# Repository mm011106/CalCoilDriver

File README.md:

<!-- 
基本資料はこちら：
BOXで、 ESM50902 を検索
SQUID用と比べて電流値が大きかも。
 -->

> [!NOTE]
> 資料などについてコメント等あればDiscussionsに投稿ください。

# 機器名
### **キャリブレーションコイルドライバ　ER-524D**

# 機器の概要

## 用途・目的
<!-- 本製品は磁気センサの感度・位置校正を行うための基準磁場を発生するためのコイルを定電流駆動する駆動回路です。
適切に設計・配置されたコイルでキャリブレーションコイルドライバにより基準となる磁場を発生させ、磁気センサから得られた磁場の強度信号とコイルドライバからの印加電流強度信号を以て磁気センサの感度・位置を校正することが可能です。 -->

複数の磁気センサをアレイ状に配置し磁場計測を行う場合、各センサ位置とその感度の両方を校正する必要があります。寸法や巻き数などのパラメタが管理されて製作されたコイル（キャリブレーションコイル）とそれを規定の電流で駆動する回路により基準となる磁場を発生させ、その磁場を計測することで校正が可能となります。この「キャリブレーションコイルドライバ」は校正作業に必要なキャリブレーションコイルを規定の電流で駆動するために設計された回路です。
> [!NOTE]
> 磁気センサの校正は以下の手順で行われます：
> 1. **センサとコイルの配置設定**：キャリブレーションコイル（複数）を校正対象の磁気センサに対して適切な位置に配置
> 2. **基準磁場の発生**：コイルドライバにより既知の強度の磁場を複数の異なる場所で発生させ、その磁場を校正対象のセンサで計測する
> 3. **信号計測**：発生した磁場の強度を磁気センサで測定すると同時に、コイルドライバのモニタ端子からコイルに流れた電流を計測
> 4. **校正実行**：両者の計測結果を基に磁気センサの感度と位置を校正

## 機能
- 交流の電流を各コイルに時分割で供給し駆動します。
- 各コイルの駆動はバースト波状の正弦波信号です。
- コイルを駆動する電流はパネルのスイッチで切り替えが可能です。
- コイルに流れる電流は電圧としてモニタができます。
- 流れている電流と上記のモニタ端子の電圧を測定器を用いて値づけすることにより、コイルに流れる電流値が計測できます。
- 単三型充電池4本で動作します。

## 性能
- 駆動信号周波数： 80Hz
- 駆動電流波形：正弦波
- 電流出力：200 / 100 / 20 / 10 [μAo-p]
- 駆動チャネル数：24（設計により変更可能）
 
> [!NOTE]
>  **駆動対象**
> 駆動の対象となるコイルは、十分直流インピーダンスが低く、インダクタンスが小さいことを想定しています。駆動回路の出力インピーダンスは10kΩ程度となっているため、コイルの直流インピーダンスが大きいと規定の電流を流せなくなる可能性があります（動作に支障はありません）。インダクタンスについては1mH以下を想定しています。駆動周波数80Hzでのコイルのインピーダンスが十分小さいことを条件として設計しています。
 <!-- 出力インピーダンス10kΩとして、1mH負荷のときのHPF遮断周波数は1.6MHz 一方、1mHの80Hzでのインピーダンス（リアクタンス）は0.5Ω -->

> [!NOTE]
>  **駆動回路**
> 駆動回路は高インピーダンス出力の非安定化電流源となっています。負荷接続時に定電流制御する回路は実装されていません。
> 負荷となるコイルがよく管理されて製造されているためコイルのインピーダンスのばらつきが非常に小さく、インピーダンスそのものも小さいと想定できたため、簡便な回路としました。

## バリエーション
本器の「負荷に電流を供給しその電流値を計測する」という機能により、生体磁場信号をエミュレートするための「ファントムコイル」をドライブすることに最適化した「ファントムドライバ」を作成可能です。磁場センサのキャリブレーションとは異なる電流設定（磁場強度設定）が必要な場合は出力電流の再設計が必要です。
> [!NOTE]
> **駆動電流の変更**
> 駆動電流の変更には回路定数の変更が必要となります。使用しているデバイスの性能から駆動電流の最大値は5mAo-p程度です。これ以上の電流が必要な場合は、回路定数の変更と同時にオペアンプの変更を検討してください。
>
> 

# 機器の構成 
コイルを駆動するための回路本体のみです。
キャリブレーションコイルそのものについては、この設計情報に含まれません。

# 動作の概要

### 駆動可能なコイルの数
この回路で駆動できるコイルの数は24個です。キャリブレーションコイルは３軸方向に磁場を発生させることを想定しており、３個のコイルが１つのコイルセットとなり、さらにそれを８個（３軸のコイルセットを８個）駆動できます。
駆動のための信号は多ピンコネクタ（ハーフピッチ50pin-SCSIコネクタ）に出力されますので、適宜コイルと接続するためのジグやケーブルの製作が必要となります。
> [!NOTE]
> 多ピンのコネクタは近年入手が困難になってきています。新たに製作される場合は3ピン〜6ピン程度の小型コネクタを複数利用するのが得策かと思います。

回路設計としては最大50個のコイルが駆動できるようになっていますので、ユーザの用途に応じてチャネル数を変更できます。

### 駆動波形
駆動は内部の正弦波発振回路に同期した正弦波のバースト波により時分割で行われます。駆動の様子を図示しました。
24個のコイルの駆動が1つのコイル駆動シーケンスとなり、それが繰り返されます。

まず、そのシーケンスの開始を示すため同期信号が正弦波の1周期の時間だけアサートされます。
同期信号がネゲートされると最初のコイルが駆動が始まります。
コイルは正弦波の24周期の時間だけ駆動され、1周期分の駆動休止時間が続き、次のコイルの駆動へと移ります。
最後のコイルが駆動された後、正弦波25周期分の長い駆動休止時間があり、コイルドライブの1周期が完了します。

駆動するコイルの順番やチャネル数、バースト波の波数と休止波数、正弦波の周波数は回路（HDL）で設定することができます。デフォルトでは、チャネル数24、正弦波の周波数80Hz、バースト波の波数24、休止波数1となっています。

<!-- 駆動用の正弦波は内部(DDSによる)で生成していますが、外部から供給することも可能です。この場合、信号の振幅が直接コイル駆動の電流値に変換されますので、供給する信号の振幅設定を確認してご利用ください。 -->

（下記「コイル駆動のタイミングチャート」を参照）

### 電流モニタ端子
コイルに流れる電流をモニタするための端子を備えています。
アナログ電圧出力で、0A = 1.65V となっています。
電流・電圧変換係数は、設計値で5033[V/I]となっています。

### 駆動電流の切り替え
駆動電流は、10μAo-p, 20μAo-p, 100μAo-p, 200μAo-pの４点切り替えです。
2つのトグルスイッチで設定します。

### 同期信号
24個のコイル駆動シーケンスの最初に正弦波の1周期の時間だけアサートされます。
レベルは0−3.3V、アクティブHi（正論理）です。

# 仕様
- ドライブコイル数：24
<br></br>
- 駆動電流 　(スイッチによる　4点切り替え)
  - 10/20/100/200μAo-p
<br></br>
- インターフェイス </br>
  - 同期信号出力：0−3.3Vロジック出力（正論理）
  - 駆動電流モニタ出力
    - アナログ電圧による（1.65V中心に+/-1V振幅）
    - 電流電圧変換係数：5033\[V/I] (設計値)
<br></br>
- 操作：フロントパネルトグルスイッチによる電源のOn/Off
<br></br>
- 表示
  - 電源電圧低下警告 Low-Battery（LED:赤）
  - 動作表示 (LED:緑)
<br></br>
- 電源：単三充電池（Ni-MH）4本
<br></br>

### コイル駆動のタイミングチャート
<!--  -->

### ブロック図

</br>

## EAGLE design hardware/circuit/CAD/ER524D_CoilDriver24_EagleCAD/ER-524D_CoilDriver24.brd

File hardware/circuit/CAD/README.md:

# このディレクトリについて
このディレクトリは回路図・基板CADのプロジェクトが保管されています。</br>

CADにはEAGLEを使っています。 Ki-CADでインポート可能かと思います。

## 構成
[本体](/hardware/circuit/CAD/ER524D_CoilDriver24_EagleCAD/ER-524D_CoilDriver24.sch)：本体の回路図です。

[ハーネス](/hardware/circuit/CAD/ER524D_CoilDriver24_EagleCAD/harness_set.sch):装置内の盤間配線用ハーネスの回路図です。

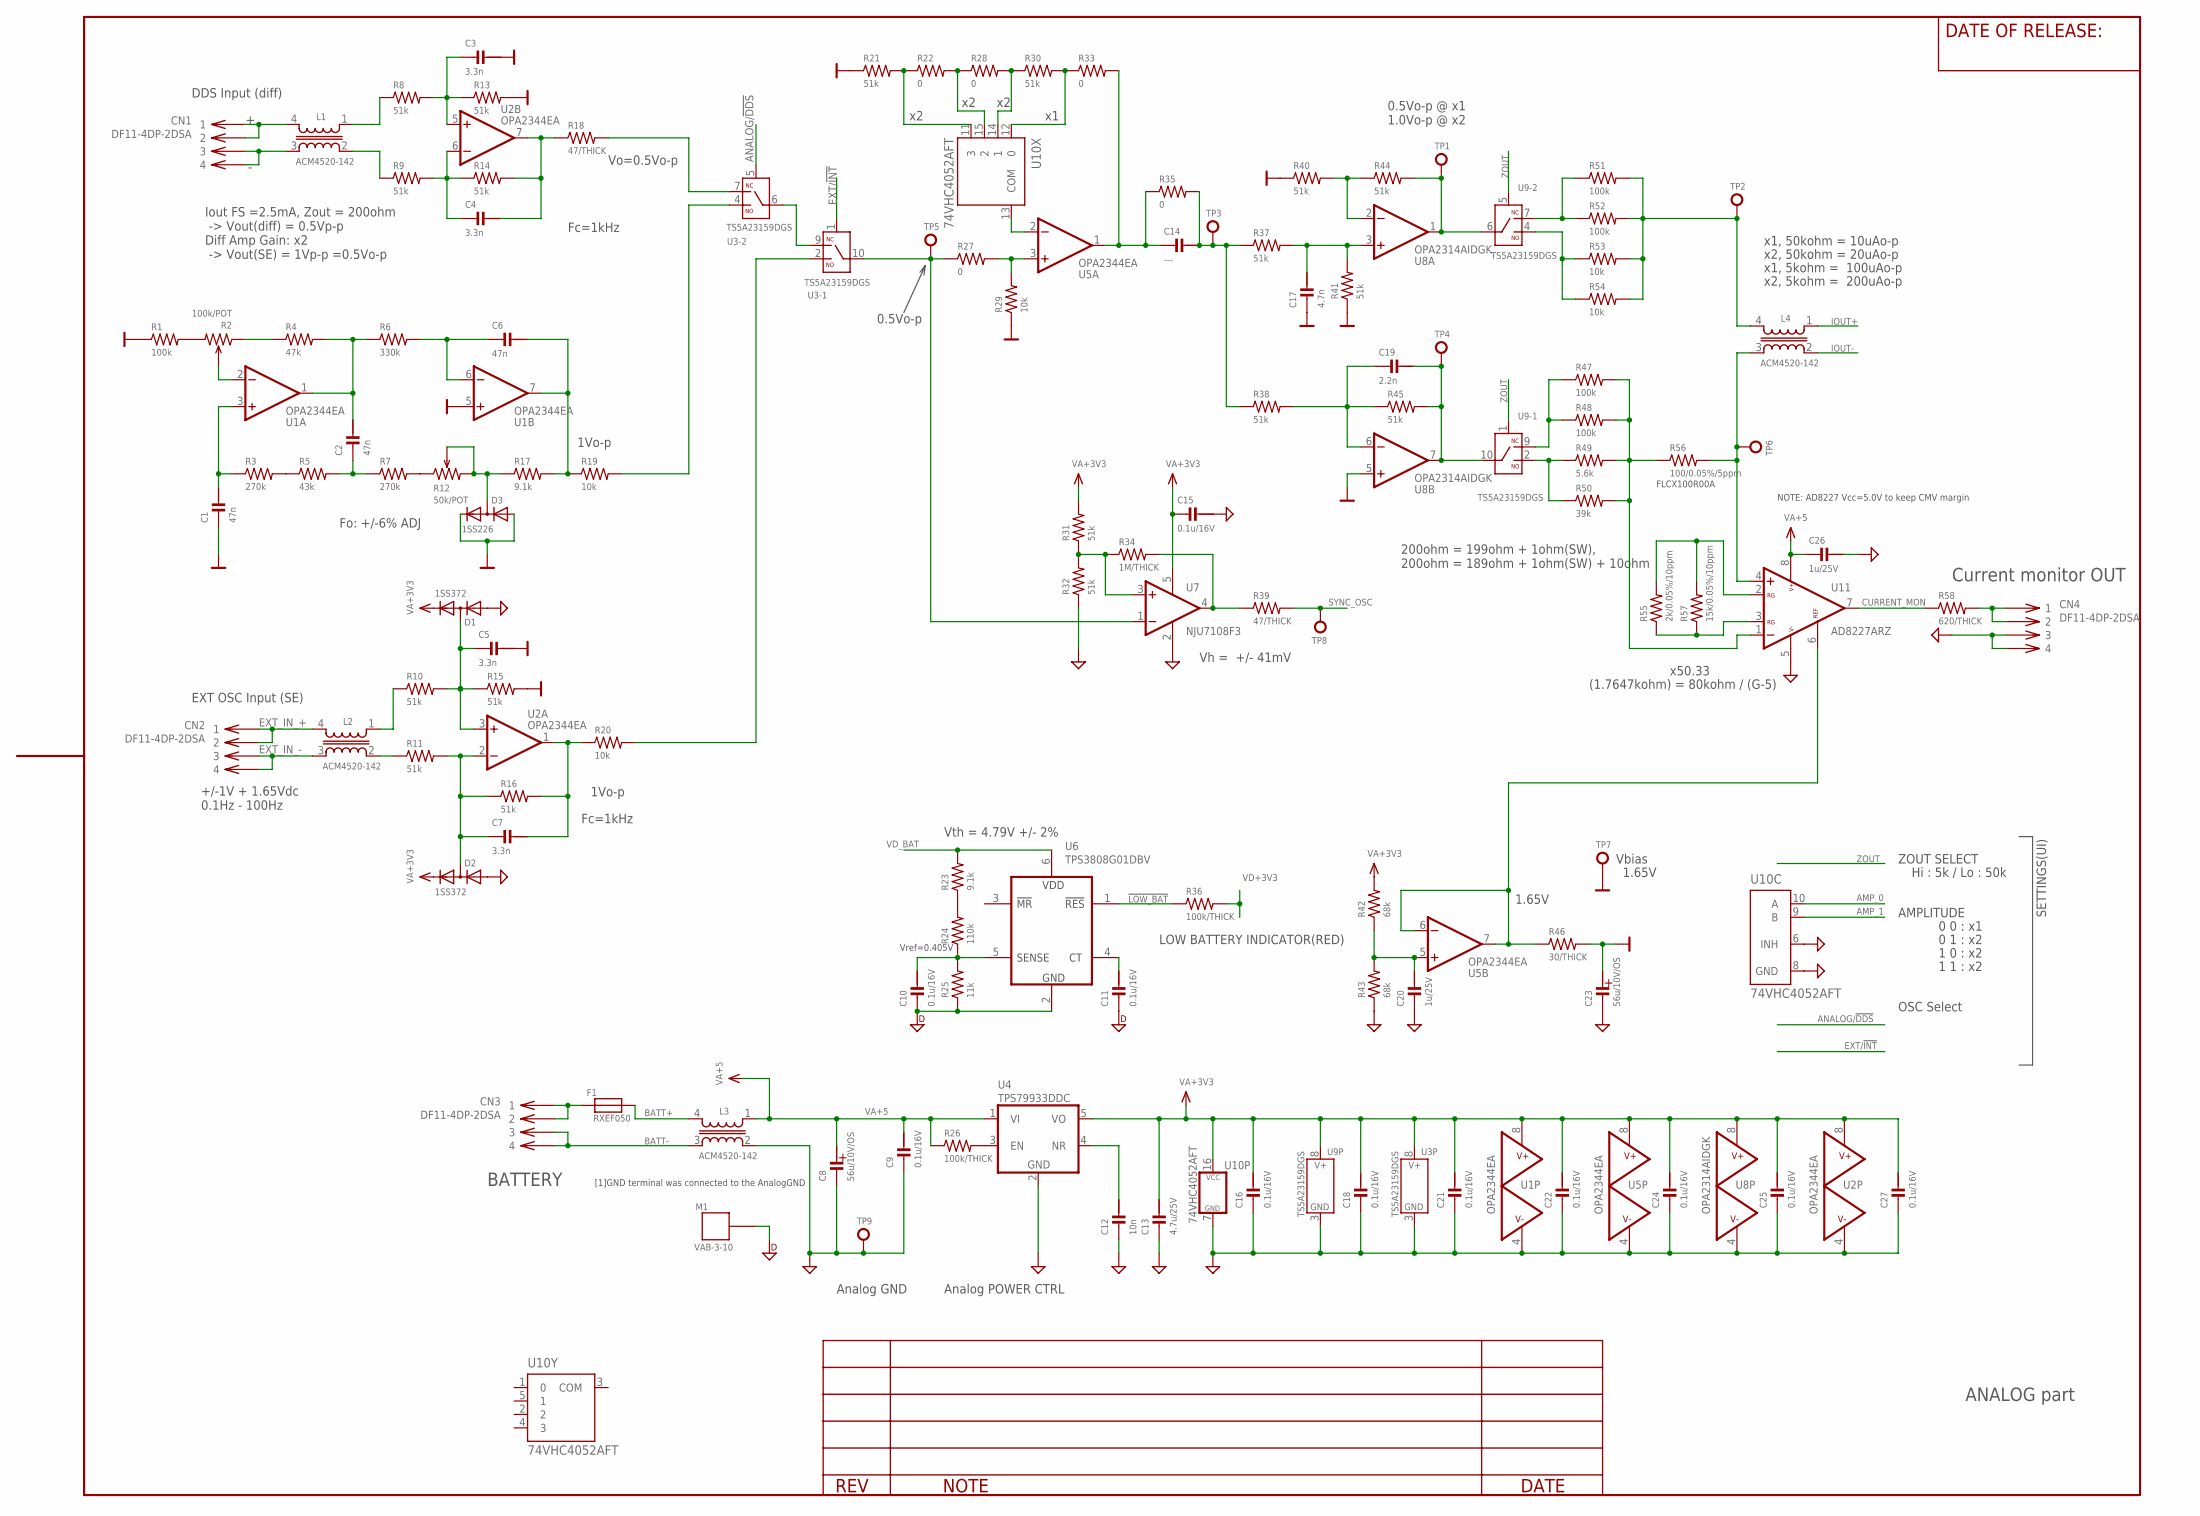
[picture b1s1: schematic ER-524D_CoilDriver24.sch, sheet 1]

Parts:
C1, C2, C6: 47n; CM3216
C3, C4, C5, C7: 3.3n; CM2012
C8, C23: 56u/10V/OS; PHI_6.3
C9, C10, C11, C15, C16, C18, C21, C22, C24, C25, C27: 0.1u/16V; CM1005
C12: 10n; CM2012
C13: 4.7u/25V; CM2012
C14: ---; CM3216
C17: 4.7n; CM2012
C19: 2.2n; CM2012
C20, C26: 1u/25V; CM1608
CN1, CN2, CN3, CN4: DF11-4DP-2DSA
D1, D2: 1SS372; SC70-3-R
D3: 1SS226; SOT23
F1: RXEF050; 8X3/5.08
L1, L2, L3, L4: ACM4520-142; ACM4520
M1: VAB-3-10; VAB_3_10_CONTACT
R1, R47, R48, R51, R52: 100k; RM1608
R2: 100k/POT; CT-6
R3, R7: 270k; RM1608
R4: 47k; RM1608
R5: 43k; RM1608
R6: 330k; RM1608
R8, R9, R10, R11, R13, R14, R15, R16, R21, R30, R31, R32, R37, R38, R40, R41, R44, R45: 51k; RM1608
R12: 50k/POT; CT-6
R17, R23: 9.1k; RM1608
R18, R39: 47/THICK; RM1608
R19, R20, R29, R53, R54: 10k; RM1608
R22, R27, R28, R33, R35: 0; RM1608
R24: 110k; RM1608
R25: 11k; RM1608
R26, R36: 100k/THICK; RM1608
R34: 1M/THICK; RM1608
R42, R43: 68k; RM1608
R46: 30/THICK; RM1608
R49: 5.6k; RM1608
R50: 39k; RM1608
R55: 2k/0.05%/10ppm; RM1608
R56: 100/0.05%/5ppm; 0204/5
R57: 15k/0.05%/10ppm; RM1608
R58: 620/THICK; RM1608
TP1, TP2, TP3, TP4, TP5, TP6, TP7, TP8, TP9: TP-LC3G; TP_TH_0R9MM
U1, U2, U5: OPA2344EA; MSO8_AEL
U3, U9: TS5A23159DGS; MSOP10
U4: TPS79933DDC; SOT-23-5
U6: TPS3808G01DBV; SOT-23
U7: NJU7108F3; SC88A
U8: OPA2314AIDGK; MSO8_AEL
U10: 74VHC4052AFT; TSSOP16-P-044-065A
U11: AD8227ARZ; SO8_AEL

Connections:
0V: C1.2, C3.1, C5.1, C17.2, C23.POS, D3.1 (A), D3.2 (C), R1.1, R13.2, R15.2, R21.1, R29.1, R40.1, R41.1, R46.2, TP7.1, U1.5 (+IN), U8.5 (+IN)
80_POWER: R26.2, U4.3 (EN)
!LOW_BAT: R36.1, U6.1 (!RESET); also elsewhere on the board
AGND: C8.NEG, C9.2, C12.2, C13.2, C15.1, C16.2, C18.2, C20.2, C21.2, C22.2, C23.NEG, C24.2, C25.2, C26.1, C27.2, CN4.3, CN4.4, D1.1 (A), D2.1 (A), L3.2 (3), R32.1, R43.1, TP9.1, U1.4 (V-), U2.4 (V-), U3.3 (V-), U4.2 (GND), U5.4 (V-), U7.2 (V-), U8.4 (V-), U9.3 (V-), U10.6 (INH), U10.7 (GND), U10.8 (GND), U11.5 (V-); also elsewhere on the board
AMP_0: U10.10 (A); also elsewhere on the board
AMP_1: U10.9 (B); also elsewhere on the board
ANALOG/!DDS!: U3.5 (IN); also elsewhere on the board
BATT+: F1.2, L3.4 (2); also elsewhere on the board
BATT-: CN3.3, CN3.4, L3.3 (4); also elsewhere on the board
CURRENT_MON: R58.1, U11.7 (OUT)
DGND: C10.2, C11.2, M1.CASE1, R25.1, U6.2 (GND); also elsewhere on the board
EXT/!INT!: U3.1 (IN); also elsewhere on the board
EXT_IN_+: CN2.1, CN2.2, L2.4 (2)
EXT_IN_-: CN2.3, CN2.4, L2.3 (4)
IOUT+: L4.1; also elsewhere on the board
IOUT-: L4.2 (3); also elsewhere on the board
unnamed: L2.1, R10.1
unnamed: U3.6 (COM), U3.9 (NC)
unnamed: R7.2, R12.1
unnamed: C3.2, R8.2, R13.1, U2.5 (+IN)
unnamed: R1.2, R2.3
unnamed: C7.2, D2.3 (AC), R11.2, R16.1, U2.2 (-IN)
unnamed: C6.1, R17.2, R19.1, U1.7 (OUT)
unnamed: L4.4 (2), R51.2, R52.2, R53.2, R54.2, TP2.1
unnamed: R21.2, R22.1, U10.11 (3)
unnamed: C7.1, R16.2, R20.1, U2.1 (OUT)
unnamed: R22.2, R28.1, U10.15 (2)
unnamed: R28.2, R30.1, U10.14 (1)
unnamed: C5.2, D1.3 (AC), R10.2, R15.1, U2.3 (+IN)
unnamed: L1.2 (3), R9.1
unnamed: R30.2, R33.1, U10.12 (0)
unnamed: C20.1, R42.1, R43.2, U5.5 (+IN)
unnamed: C19.2, R38.2, R45.1, U8.6 (-IN)
unnamed: U5.2 (-IN), U10.13 (COM)
unnamed: C14.2, R33.2, R35.1, U5.1 (OUT)
unnamed: R27.2, R29.2, U5.3 (+IN)
unnamed: C19.1, R45.2, TP4.1, U8.7 (OUT), U9.10 (COM)
unnamed: R44.2, TP1.1, U8.1 (OUT), U9.6 (COM)
unnamed: R40.2, R44.1, U8.2 (-IN)
unnamed: C17.1, R37.2, R41.2, U8.3 (+IN)
unnamed: R49.1, R50.1, U9.2 (NO)
unnamed: R47.1, R48.1, U9.9 (NC)
unnamed: R47.2, R48.2, R49.2, R50.2, R56.1, U11.1 (-IN)
unnamed: R51.1, R52.1, U9.7 (NC)
unnamed: R53.1, R54.1, U9.4 (NO)
unnamed: C4.1, R14.2, R18.1, U2.7 (OUT)
unnamed: R2.1, R4.1
unnamed: C2.1, R4.2, R6.1, U1.1 (OUT)
unnamed: C6.2, R6.2, U1.6 (-IN)
unnamed: R2.2, U1.2 (-IN)
unnamed: C1.1, R3.1, U1.3 (+IN)
unnamed: R3.2, R5.1
unnamed: C2.2, R5.2, R7.1
unnamed: D3.3 (AC), R12.2, R12.3, R17.1
unnamed: C14.1, R35.2, R37.1, R38.1, TP3.1
unnamed: L4.3 (4), R56.2, TP6.1, U11.4 (+IN)
unnamed: C4.2, R9.2, R14.1, U2.6 (-IN)
unnamed: CN1.3, CN1.4, L1.3 (4)
unnamed: CN1.1, CN1.2, L1.4 (2)
unnamed: R31.1, R32.2, R34.1, U7.3 (+IN)
unnamed: R34.2, R39.1, U7.4 (OUT)
unnamed: CN3.1, CN3.2, F1.1
unnamed: C11.1, U6.4 (CT)
unnamed: L1.1, R8.1
unnamed: C10.1, R24.1, R25.2, U6.5 (SENSE)
unnamed: CN4.1, CN4.2, R58.2
unnamed: C12.1, U4.4 (NR)
unnamed: L2.2 (3), R11.1
unnamed: R20.2, U3.2 (NO)
unnamed: R18.2, U3.7 (NC)
unnamed: R27.1, TP5.1, U3.10 (COM), U7.1 (-IN)
unnamed: R19.2, U3.4 (NO)
unnamed: R23.1, R24.2
unnamed: R55.1, R57.1, U11.3 (RG2)
unnamed: R55.2, R57.2, U11.2 (RG1)
unnamed: R46.1, U5.6 (-IN), U5.7 (OUT), U11.6 (REF)
SYNC_OSC: R39.2, TP8.1; also elsewhere on the board
VA+3V3: C13.1, C15.2, C16.1, C18.1, C21.1, C22.1, C24.1, C25.1, C27.1, D1.2 (C), D2.2 (C), R31.2, R42.2, U1.8 (V+), U2.8 (V+), U3.8 (V+), U4.5 (VO), U5.8 (V+), U7.5 (V+), U8.8 (V+), U9.8 (V+), U10.16 (VCC); also elsewhere on the board
VA+5: C8.POS, C9.1, C26.2, L3.1, R26.1, U4.1 (VI), U11.8 (V+)
VD+3V3: R36.2; also elsewhere on the board
VD_BAT: R23.2, U6.6 (VDD); also elsewhere on the board
ZOUT: U9.1 (IN), U9.5 (IN); also elsewhere on the board

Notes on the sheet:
ANALOG part
AMPLITUDE
ZOUT SELECT
Hi : 5k / Lo : 50k
0 0 : x1
0 1 : x2
1 0 : x2
1 1 : x2
LOW BATTERY INDICATOR(RED)
Vth = 4.79V +/- 2%
Vref=0.405V
Analog GND
Analog POWER CTRL
1.65V
Vh = +/- 41mV
Vbias
Fo: +/-6% ADJ
x1, 50kohm = 10uAo-p
x2, 50kohm = 20uAo-p
x1, 5kohm = 100uAo-p
x2, 5kohm = 200uAo-p
0.5Vo-p
x50.33
DDS Input (diff)
Vo=0.5Vo-p
Fc=1kHz
[1]GND terminal was connected to the AnalogGND
BATTERY
Current monitor OUT
NOTE: AD8227 Vcc=5.0V to keep CMV margin
Iout FS =2.5mA, Zout = 200ohm -> Vout(diff) = 0.5Vp-p Diff Amp Gain: x2 -> Vout(SE) = 1Vp-p =0.5Vo-p
1Vo-p
EXT OSC Input (SE)
+/-1V + 1.65Vdc 0.1Hz - 100Hz
OSC Select
200ohm = 199ohm + 1ohm(SW), 200ohm = 189ohm + 1ohm(SW) + 10ohm
SETTINGS(UI)
0.5Vo-p @ x1 1.0Vo-p @ x2
(1.7647kohm) = 80kohm / (G-5)
FLCX100R00A

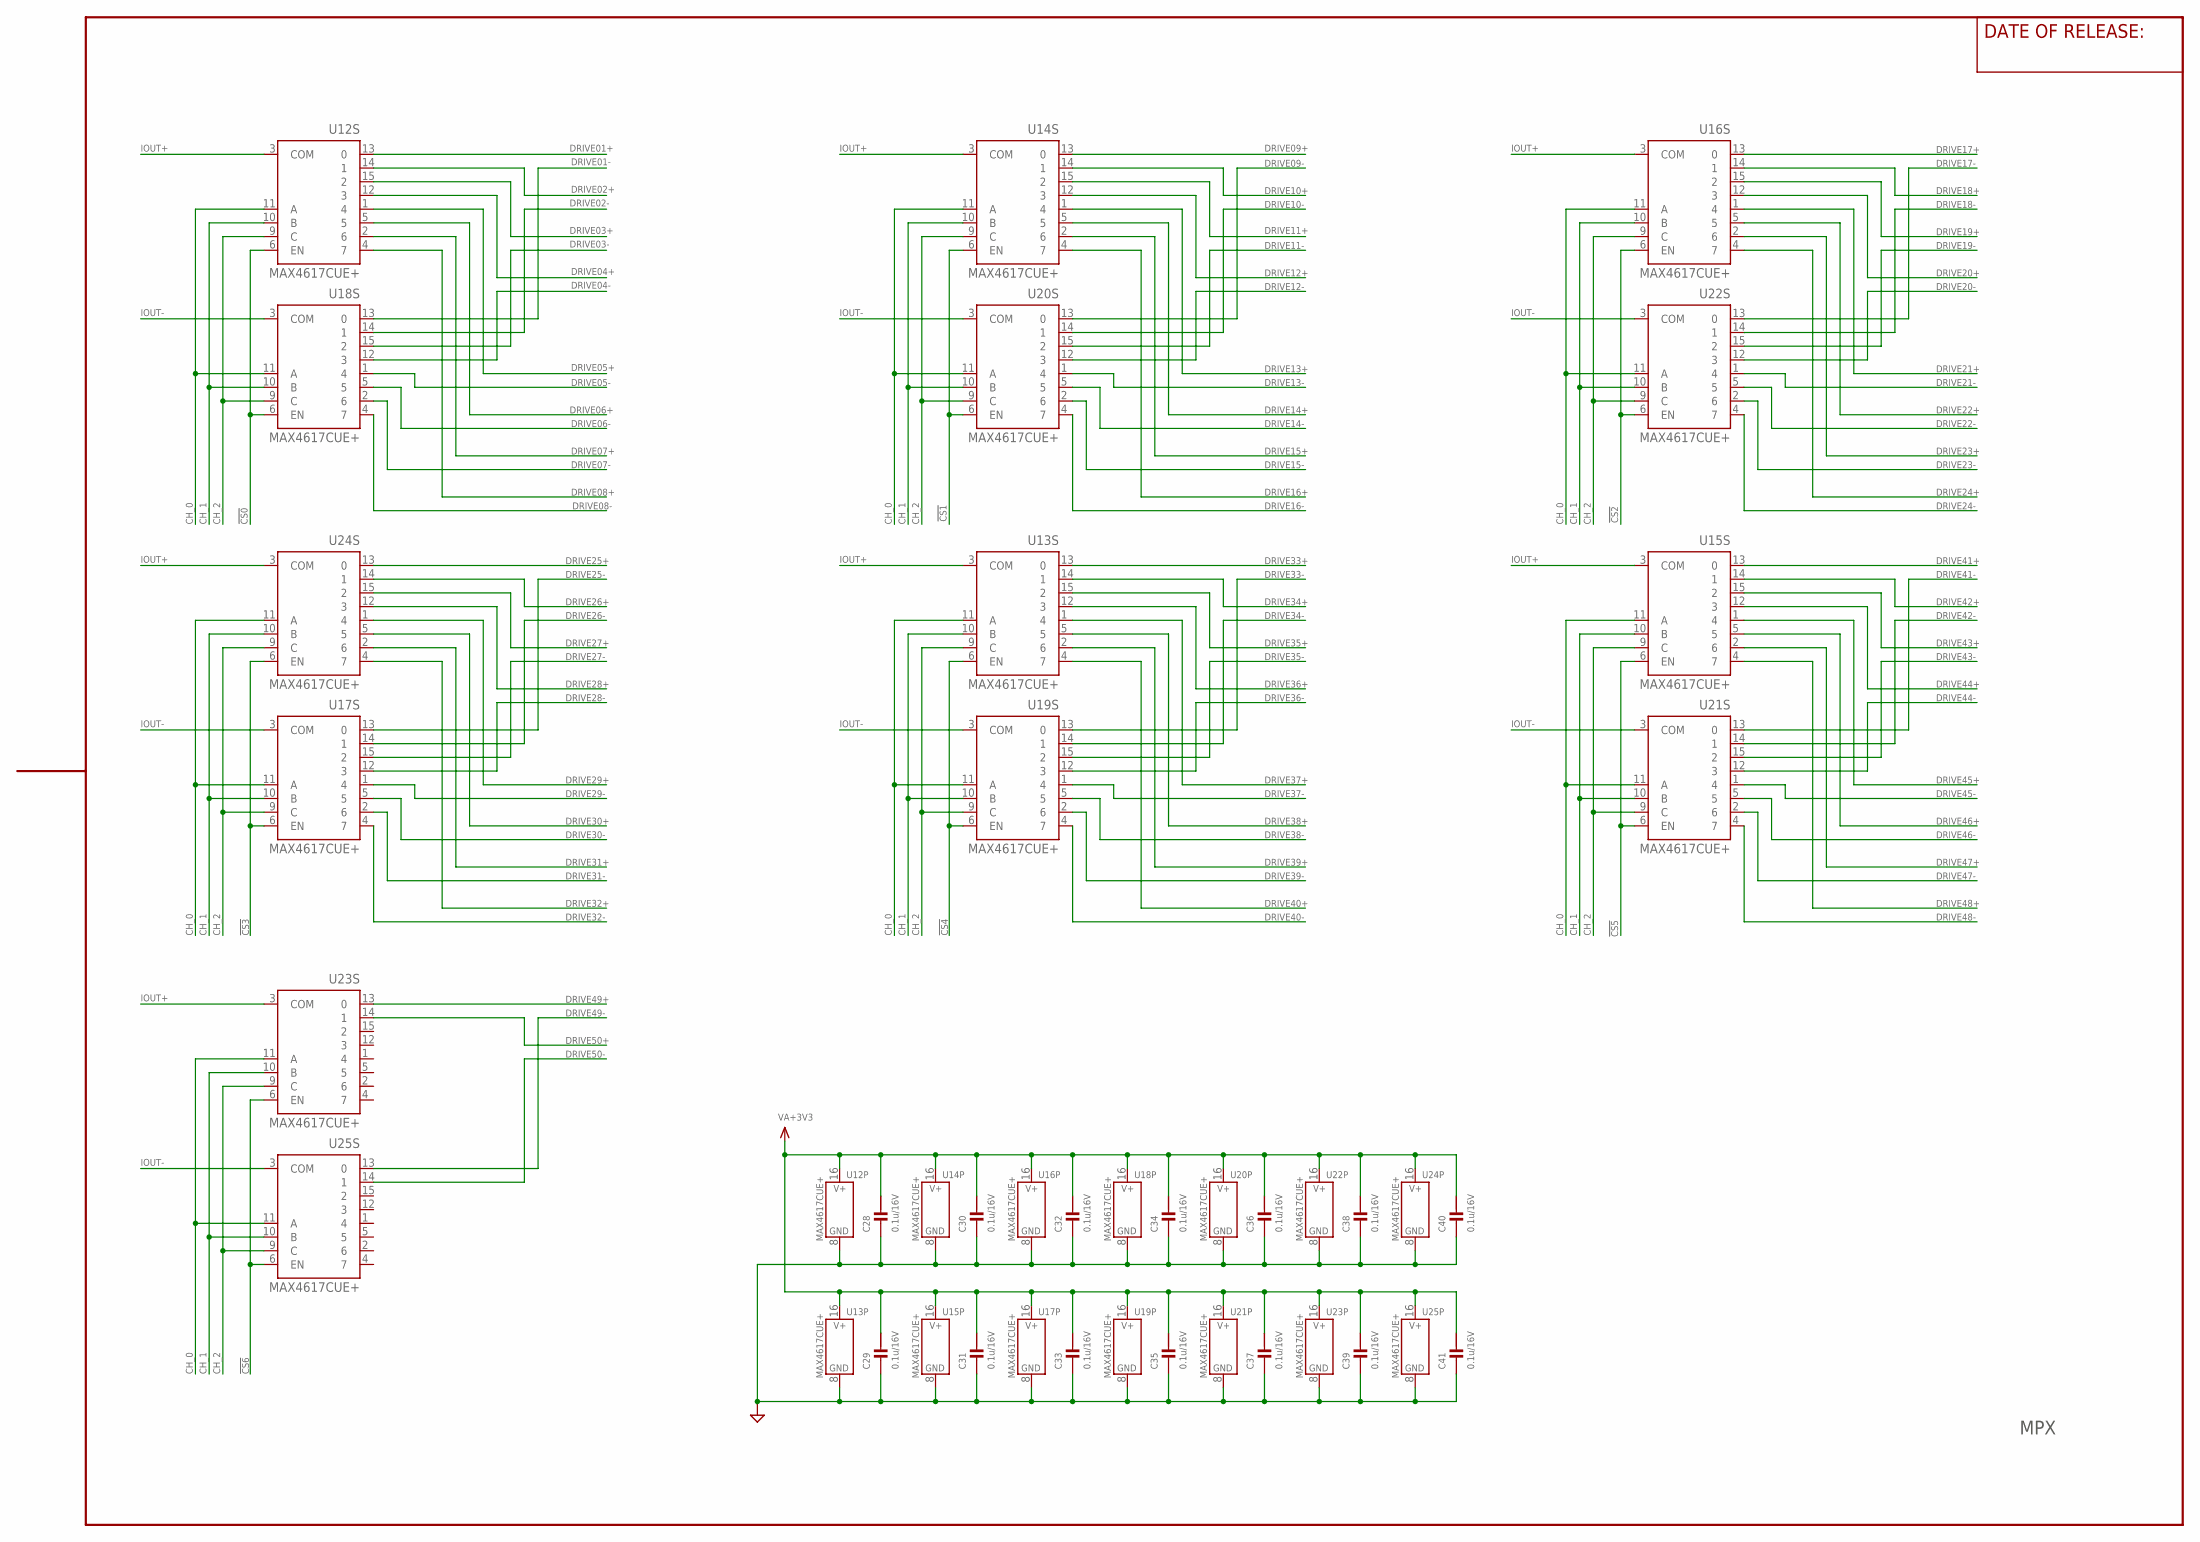
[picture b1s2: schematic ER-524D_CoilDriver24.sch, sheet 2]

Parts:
C28, C29, C30, C31, C32, C33, C34, C35, C36, C37, C38, C39, C40, C41: 0.1u/16V; CM1005
U12, U13, U14, U15, U16, U17, U18, U19, U20, U21, U22, U23, U24, U25: MAX4617CUE+; TSSOP16_AEL

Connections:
!CS0: U12.6 (EN), U18.6 (EN); also elsewhere on the board
!CS1: U14.6 (EN), U20.6 (EN); also elsewhere on the board
!CS2: U16.6 (EN), U22.6 (EN); also elsewhere on the board
!CS3: U17.6 (EN), U24.6 (EN); also elsewhere on the board
!CS4: U13.6 (EN), U19.6 (EN); also elsewhere on the board
!CS5: U15.6 (EN), U21.6 (EN); also elsewhere on the board
!CS6: U23.6 (EN), U25.6 (EN); also elsewhere on the board
AGND: C28.2, C29.2, C30.2, C31.2, C32.2, C33.2, C34.2, C35.2, C36.2, C37.2, C38.2, C39.2, C40.2, C41.2, U12.8 (V-), U13.8 (V-), U14.8 (V-), U15.8 (V-), U16.8 (V-), U17.8 (V-), U18.8 (V-), U19.8 (V-), U20.8 (V-), U21.8 (V-), U22.8 (V-), U23.8 (V-), U24.8 (V-), U25.8 (V-); also elsewhere on the board
CH_0: U12.11 (A), U13.11 (A), U14.11 (A), U15.11 (A), U16.11 (A), U17.11 (A), U18.11 (A), U19.11 (A), U20.11 (A), U21.11 (A), U22.11 (A), U23.11 (A), U24.11 (A), U25.11 (A); also elsewhere on the board
CH_1: U12.10 (B), U13.10 (B), U14.10 (B), U15.10 (B), U16.10 (B), U17.10 (B), U18.10 (B), U19.10 (B), U20.10 (B), U21.10 (B), U22.10 (B), U23.10 (B), U24.10 (B), U25.10 (B); also elsewhere on the board
CH_2: U12.9 (C), U13.9 (C), U14.9 (C), U15.9 (C), U16.9 (C), U17.9 (C), U18.9 (C), U19.9 (C), U20.9 (C), U21.9 (C), U22.9 (C), U23.9 (C), U24.9 (C), U25.9 (C); also elsewhere on the board
DRIVE01+: U12.13 (0); also elsewhere on the board
DRIVE01-: U18.13 (0); also elsewhere on the board
DRIVE02+: U12.14 (1); also elsewhere on the board
DRIVE02-: U18.14 (1); also elsewhere on the board
DRIVE03+: U12.15 (2); also elsewhere on the board
DRIVE03-: U18.15 (2); also elsewhere on the board
DRIVE04+: U12.12 (3); also elsewhere on the board
DRIVE04-: U18.12 (3); also elsewhere on the board
DRIVE05+: U12.1 (4); also elsewhere on the board
DRIVE05-: U18.1 (4); also elsewhere on the board
DRIVE06+: U12.5; also elsewhere on the board
DRIVE06-: U18.5; also elsewhere on the board
DRIVE07+: U12.2 (6); also elsewhere on the board
DRIVE07-: U18.2 (6); also elsewhere on the board
DRIVE08+: U12.4 (7); also elsewhere on the board
DRIVE08-: U18.4 (7); also elsewhere on the board
DRIVE09+: U14.13 (0); also elsewhere on the board
DRIVE09-: U20.13 (0); also elsewhere on the board
DRIVE10+: U14.14 (1); also elsewhere on the board
DRIVE10-: U20.14 (1); also elsewhere on the board
DRIVE11+: U14.15 (2); also elsewhere on the board
DRIVE11-: U20.15 (2); also elsewhere on the board
DRIVE12+: U14.12 (3); also elsewhere on the board
DRIVE12-: U20.12 (3); also elsewhere on the board
DRIVE13+: U14.1 (4); also elsewhere on the board
DRIVE13-: U20.1 (4); also elsewhere on the board
DRIVE14+: U14.5; also elsewhere on the board
DRIVE14-: U20.5; also elsewhere on the board
DRIVE15+: U14.2 (6); also elsewhere on the board
DRIVE15-: U20.2 (6); also elsewhere on the board
DRIVE16+: U14.4 (7); also elsewhere on the board
DRIVE16-: U20.4 (7); also elsewhere on the board
DRIVE17+: U16.13 (0); also elsewhere on the board
DRIVE17-: U22.13 (0); also elsewhere on the board
DRIVE18+: U16.14 (1); also elsewhere on the board
DRIVE18-: U22.14 (1); also elsewhere on the board
DRIVE19+: U16.15 (2); also elsewhere on the board
DRIVE19-: U22.15 (2); also elsewhere on the board
DRIVE20+: U16.12 (3); also elsewhere on the board
DRIVE20-: U22.12 (3); also elsewhere on the board
DRIVE21+: U16.1 (4); also elsewhere on the board
DRIVE21-: U22.1 (4); also elsewhere on the board
DRIVE22+: U16.5; also elsewhere on the board
DRIVE22-: U22.5; also elsewhere on the board
DRIVE23+: U16.2 (6); also elsewhere on the board
DRIVE23-: U22.2 (6); also elsewhere on the board
DRIVE24+: U16.4 (7); also elsewhere on the board
DRIVE24-: U22.4 (7); also elsewhere on the board
DRIVE25+: U24.13 (0); also elsewhere on the board
DRIVE25-: U17.13 (0); also elsewhere on the board
DRIVE26+: U24.14 (1); also elsewhere on the board
DRIVE26-: U17.14 (1); also elsewhere on the board
DRIVE27+: U24.15 (2); also elsewhere on the board
DRIVE27-: U17.15 (2); also elsewhere on the board
DRIVE28+: U24.12 (3); also elsewhere on the board
DRIVE28-: U17.12 (3); also elsewhere on the board
DRIVE29+: U24.1 (4); also elsewhere on the board
DRIVE29-: U17.1 (4); also elsewhere on the board
DRIVE30+: U24.5; also elsewhere on the board
DRIVE30-: U17.5; also elsewhere on the board
DRIVE31+: U24.2 (6); also elsewhere on the board
DRIVE31-: U17.2 (6); also elsewhere on the board
DRIVE32+: U24.4 (7); also elsewhere on the board
DRIVE32-: U17.4 (7); also elsewhere on the board
DRIVE33+: U13.13 (0); also elsewhere on the board
DRIVE33-: U19.13 (0); also elsewhere on the board
DRIVE34+: U13.14 (1); also elsewhere on the board
DRIVE34-: U19.14 (1); also elsewhere on the board
DRIVE35+: U13.15 (2); also elsewhere on the board
DRIVE35-: U19.15 (2); also elsewhere on the board
DRIVE36+: U13.12 (3); also elsewhere on the board
DRIVE36-: U19.12 (3); also elsewhere on the board
DRIVE37+: U13.1 (4); also elsewhere on the board
DRIVE37-: U19.1 (4); also elsewhere on the board
DRIVE38+: U13.5; also elsewhere on the board
DRIVE38-: U19.5; also elsewhere on the board
DRIVE39+: U13.2 (6); also elsewhere on the board
DRIVE39-: U19.2 (6); also elsewhere on the board
DRIVE40+: U13.4 (7); also elsewhere on the board
DRIVE40-: U19.4 (7); also elsewhere on the board
DRIVE41+: U15.13 (0); also elsewhere on the board
DRIVE41-: U21.13 (0); also elsewhere on the board
DRIVE42+: U15.14 (1); also elsewhere on the board
DRIVE42-: U21.14 (1); also elsewhere on the board
DRIVE43+: U15.15 (2); also elsewhere on the board
DRIVE43-: U21.15 (2); also elsewhere on the board
DRIVE44+: U15.12 (3); also elsewhere on the board
DRIVE44-: U21.12 (3); also elsewhere on the board
DRIVE45+: U15.1 (4); also elsewhere on the board
DRIVE45-: U21.1 (4); also elsewhere on the board
DRIVE46+: U15.5; also elsewhere on the board
DRIVE46-: U21.5; also elsewhere on the board
DRIVE47+: U15.2 (6); also elsewhere on the board
DRIVE47-: U21.2 (6); also elsewhere on the board
DRIVE48+: U15.4 (7); also elsewhere on the board
DRIVE48-: U21.4 (7); also elsewhere on the board
DRIVE49+: U23.13 (0); also elsewhere on the board
DRIVE49-: U25.13 (0); also elsewhere on the board
DRIVE50+: U23.14 (1); also elsewhere on the board
DRIVE50-: U25.14 (1); also elsewhere on the board
IOUT+: U12.3 (COM), U13.3 (COM), U14.3 (COM), U15.3 (COM), U16.3 (COM), U23.3 (COM), U24.3 (COM); also elsewhere on the board
IOUT-: U17.3 (COM), U18.3 (COM), U19.3 (COM), U20.3 (COM), U21.3 (COM), U22.3 (COM), U25.3 (COM); also elsewhere on the board
VA+3V3: C28.1, C29.1, C30.1, C31.1, C32.1, C33.1, C34.1, C35.1, C36.1, C37.1, C38.1, C39.1, C40.1, C41.1, U12.16 (V+), U13.16 (V+), U14.16 (V+), U15.16 (V+), U16.16 (V+), U17.16 (V+), U18.16 (V+), U19.16 (V+), U20.16 (V+), U21.16 (V+), U22.16 (V+), U23.16 (V+), U24.16 (V+), U25.16 (V+); also elsewhere on the board

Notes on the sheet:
MPX

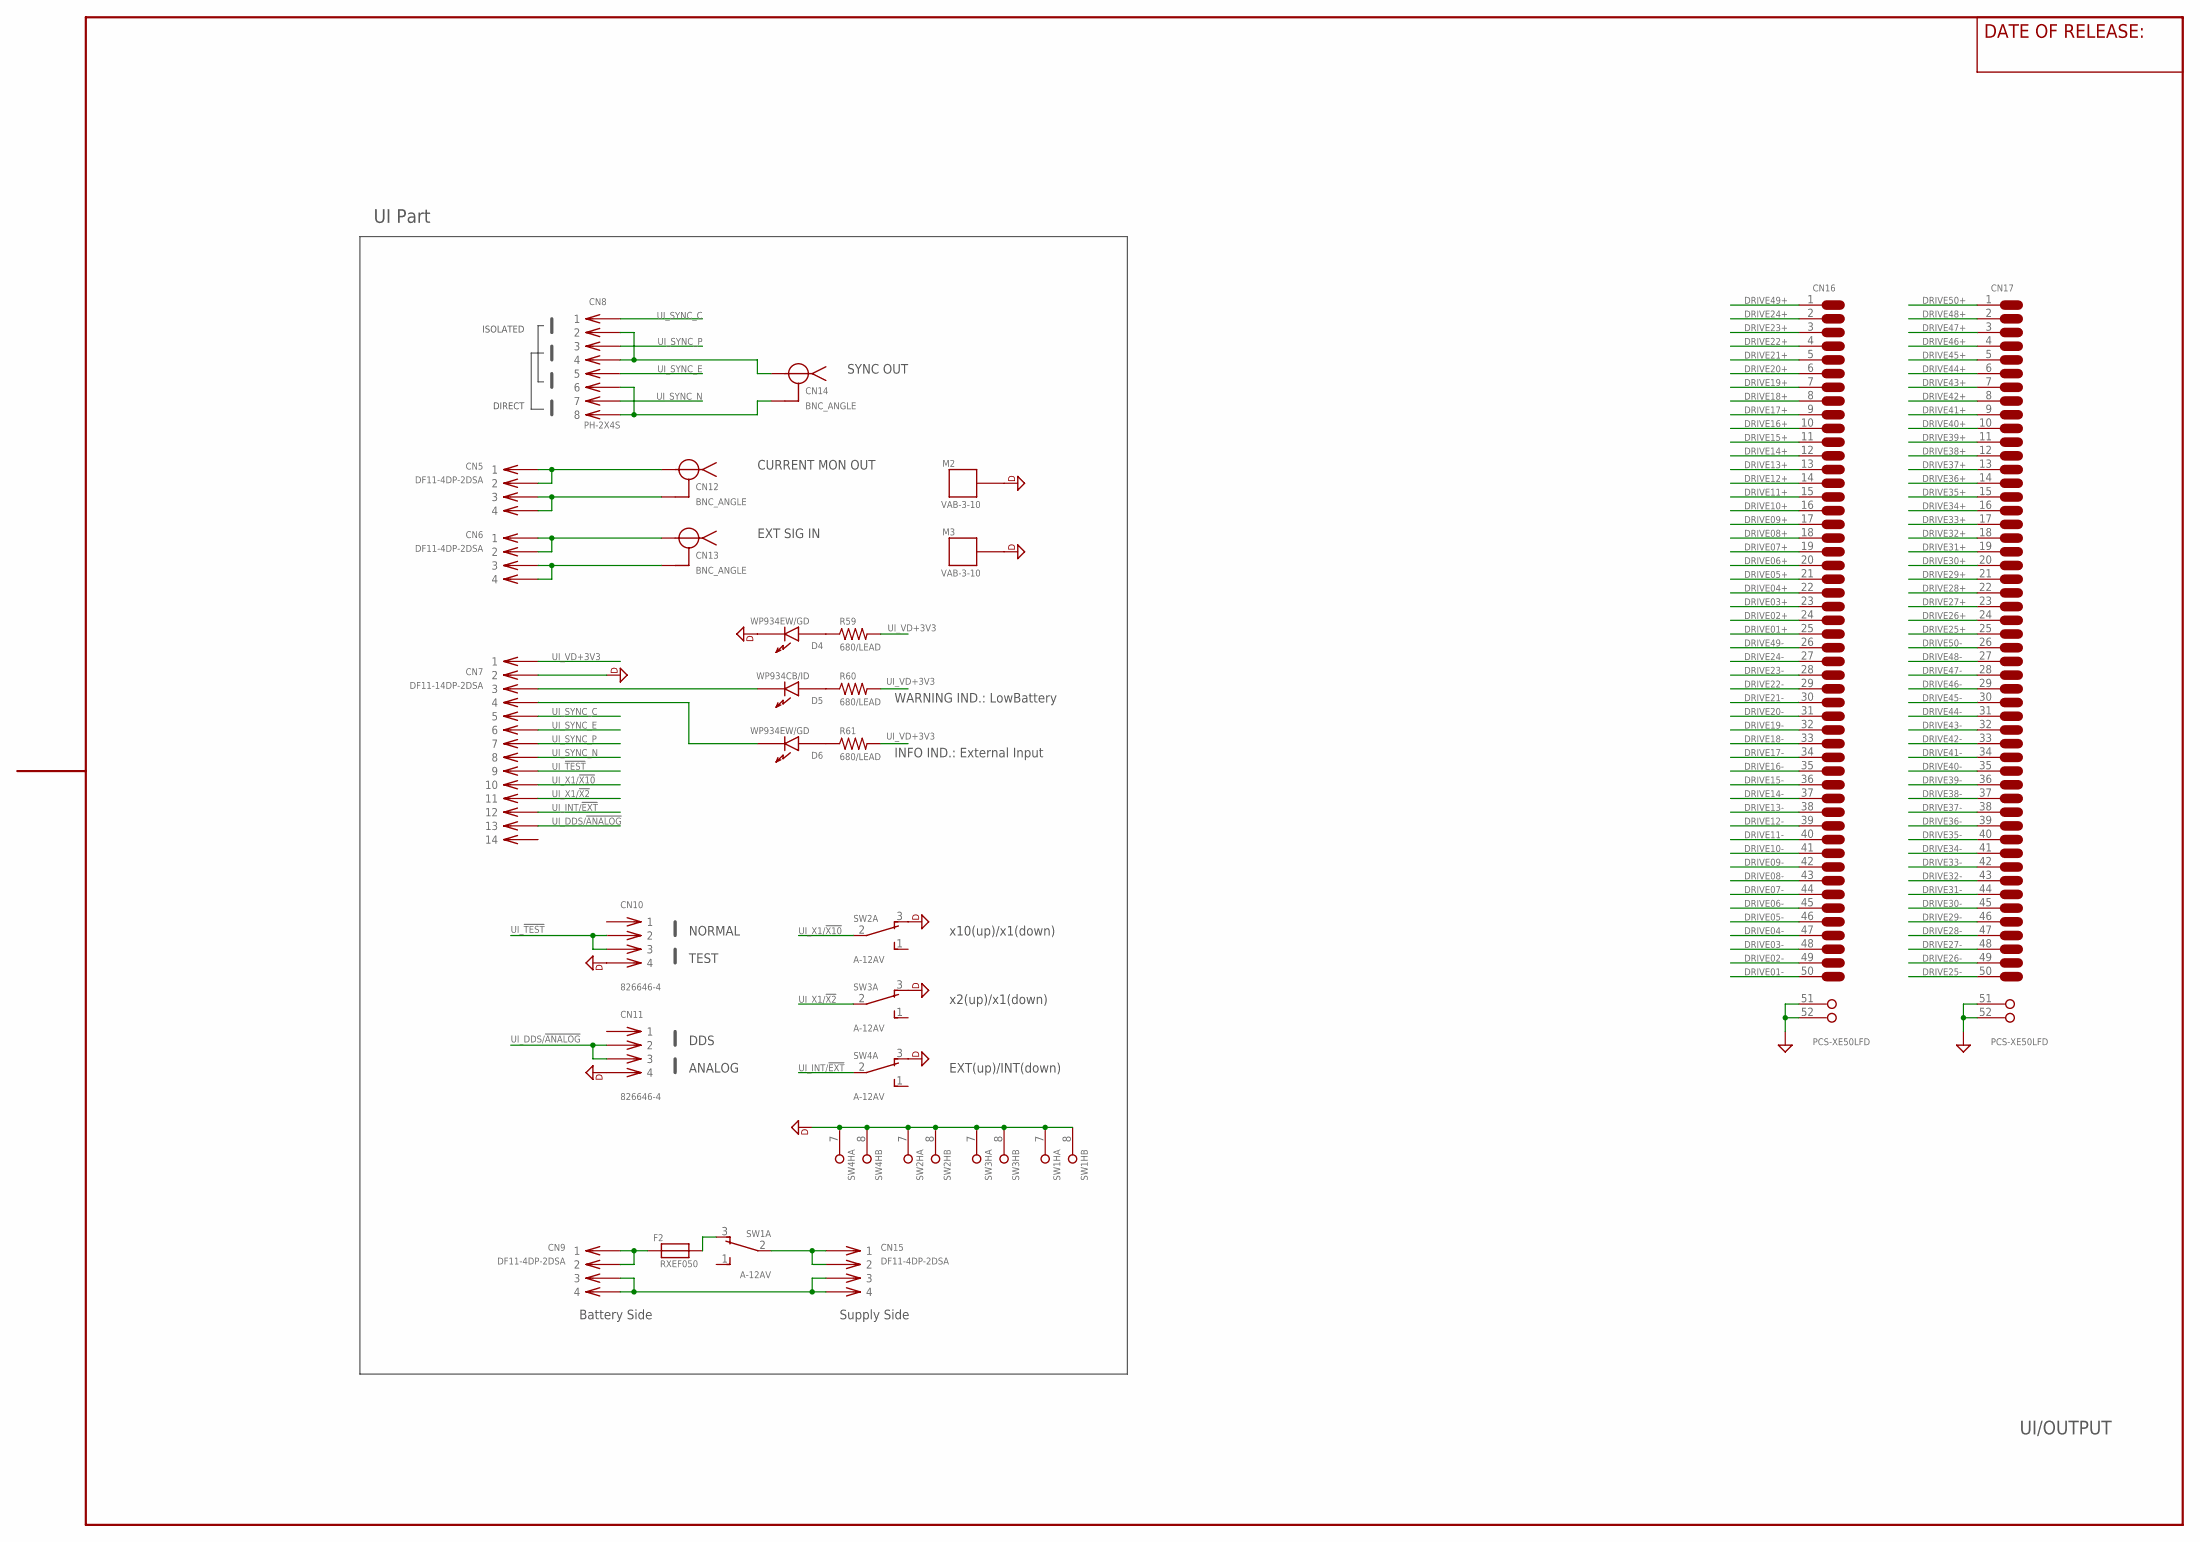
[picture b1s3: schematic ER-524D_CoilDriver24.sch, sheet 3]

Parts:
CN5, CN6, CN9, CN15: DF11-4DP-2DSA
CN7: DF11-14DP-2DSA
CN8: PH-2X4S; PIN_HEADER_8PIN
CN10, CN11: 826646-4; PIN_HEADER_4PIN
CN12, CN13, CN14: BNC_ANGLE; BNC_F_ANGLE
CN16, CN17: PCS-XE50LFD; 50LFD2
D4, D6: WP934EW/GD; L-93A8CB
D5: WP934CB/ID; L-93A8CB
F2: RXEF050; 8X3/5.08
M2, M3: VAB-3-10; VAB_3_10_CONTACT
R59, R60, R61: 680/LEAD; 0207/2V
SW1, SW2, SW3, SW4: A-12AV; A-12*

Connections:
AGND: CN16.51 (G1), CN16.52 (G2), CN17.51 (G1), CN17.52 (G2); also elsewhere on the board
DGND: CN7.2, CN10.4, CN11.4, D4.C (K1), M2.CASE1, M3.CASE1, SW1.7 (BRACKET), SW1.8 (BRACKET), SW2.3 (NC), SW2.7 (BRACKET), SW2.8 (BRACKET), SW3.3 (NC), SW3.7 (BRACKET), SW3.8 (BRACKET), SW4.3 (NC), SW4.7 (BRACKET), SW4.8 (BRACKET); also elsewhere on the board
DRIVE01+: CN16.25; also elsewhere on the board
DRIVE01-: CN16.50; also elsewhere on the board
DRIVE02+: CN16.24; also elsewhere on the board
DRIVE02-: CN16.49; also elsewhere on the board
DRIVE03+: CN16.23; also elsewhere on the board
DRIVE03-: CN16.48; also elsewhere on the board
DRIVE04+: CN16.22; also elsewhere on the board
DRIVE04-: CN16.47; also elsewhere on the board
DRIVE05+: CN16.21; also elsewhere on the board
DRIVE05-: CN16.46; also elsewhere on the board
DRIVE06+: CN16.20; also elsewhere on the board
DRIVE06-: CN16.45; also elsewhere on the board
DRIVE07+: CN16.19; also elsewhere on the board
DRIVE07-: CN16.44; also elsewhere on the board
DRIVE08+: CN16.18; also elsewhere on the board
DRIVE08-: CN16.43; also elsewhere on the board
DRIVE09+: CN16.17; also elsewhere on the board
DRIVE09-: CN16.42; also elsewhere on the board
DRIVE10+: CN16.16; also elsewhere on the board
DRIVE10-: CN16.41; also elsewhere on the board
DRIVE11+: CN16.15; also elsewhere on the board
DRIVE11-: CN16.40; also elsewhere on the board
DRIVE12+: CN16.14; also elsewhere on the board
DRIVE12-: CN16.39; also elsewhere on the board
DRIVE13+: CN16.13; also elsewhere on the board
DRIVE13-: CN16.38; also elsewhere on the board
DRIVE14+: CN16.12; also elsewhere on the board
DRIVE14-: CN16.37; also elsewhere on the board
DRIVE15+: CN16.11; also elsewhere on the board
DRIVE15-: CN16.36; also elsewhere on the board
DRIVE16+: CN16.10; also elsewhere on the board
DRIVE16-: CN16.35; also elsewhere on the board
DRIVE17+: CN16.9; also elsewhere on the board
DRIVE17-: CN16.34; also elsewhere on the board
DRIVE18+: CN16.8; also elsewhere on the board
DRIVE18-: CN16.33; also elsewhere on the board
DRIVE19+: CN16.7; also elsewhere on the board
DRIVE19-: CN16.32; also elsewhere on the board
DRIVE20+: CN16.6; also elsewhere on the board
DRIVE20-: CN16.31; also elsewhere on the board
DRIVE21+: CN16.5; also elsewhere on the board
DRIVE21-: CN16.30; also elsewhere on the board
DRIVE22+: CN16.4; also elsewhere on the board
DRIVE22-: CN16.29; also elsewhere on the board
DRIVE23+: CN16.3; also elsewhere on the board
DRIVE23-: CN16.28; also elsewhere on the board
DRIVE24+: CN16.2; also elsewhere on the board
DRIVE24-: CN16.27; also elsewhere on the board
DRIVE25+: CN17.25; also elsewhere on the board
DRIVE25-: CN17.50; also elsewhere on the board
DRIVE26+: CN17.24; also elsewhere on the board
DRIVE26-: CN17.49; also elsewhere on the board
DRIVE27+: CN17.23; also elsewhere on the board
DRIVE27-: CN17.48; also elsewhere on the board
DRIVE28+: CN17.22; also elsewhere on the board
DRIVE28-: CN17.47; also elsewhere on the board
DRIVE29+: CN17.21; also elsewhere on the board
DRIVE29-: CN17.46; also elsewhere on the board
DRIVE30+: CN17.20; also elsewhere on the board
DRIVE30-: CN17.45; also elsewhere on the board
DRIVE31+: CN17.19; also elsewhere on the board
DRIVE31-: CN17.44; also elsewhere on the board
DRIVE32+: CN17.18; also elsewhere on the board
DRIVE32-: CN17.43; also elsewhere on the board
DRIVE33+: CN17.17; also elsewhere on the board
DRIVE33-: CN17.42; also elsewhere on the board
DRIVE34+: CN17.16; also elsewhere on the board
DRIVE34-: CN17.41; also elsewhere on the board
DRIVE35+: CN17.15; also elsewhere on the board
DRIVE35-: CN17.40; also elsewhere on the board
DRIVE36+: CN17.14; also elsewhere on the board
DRIVE36-: CN17.39; also elsewhere on the board
DRIVE37+: CN17.13; also elsewhere on the board
DRIVE37-: CN17.38; also elsewhere on the board
DRIVE38+: CN17.12; also elsewhere on the board
DRIVE38-: CN17.37; also elsewhere on the board
DRIVE39+: CN17.11; also elsewhere on the board
DRIVE39-: CN17.36; also elsewhere on the board
DRIVE40+: CN17.10; also elsewhere on the board
DRIVE40-: CN17.35; also elsewhere on the board
DRIVE41+: CN17.9; also elsewhere on the board
DRIVE41-: CN17.34; also elsewhere on the board
DRIVE42+: CN17.8; also elsewhere on the board
DRIVE42-: CN17.33; also elsewhere on the board
DRIVE43+: CN17.7; also elsewhere on the board
DRIVE43-: CN17.32; also elsewhere on the board
DRIVE44+: CN17.6; also elsewhere on the board
DRIVE44-: CN17.31; also elsewhere on the board
DRIVE45+: CN17.5; also elsewhere on the board
DRIVE45-: CN17.30; also elsewhere on the board
DRIVE46+: CN17.4; also elsewhere on the board
DRIVE46-: CN17.29; also elsewhere on the board
DRIVE47+: CN17.3; also elsewhere on the board
DRIVE47-: CN17.28; also elsewhere on the board
DRIVE48+: CN17.2; also elsewhere on the board
DRIVE48-: CN17.27; also elsewhere on the board
DRIVE49+: CN16.1; also elsewhere on the board
DRIVE49-: CN16.26; also elsewhere on the board
DRIVE50+: CN17.1; also elsewhere on the board
DRIVE50-: CN17.26; also elsewhere on the board
unnamed: CN7.3, D5.C (K1)
unnamed: D5.A (A1), R60.1
unnamed: D6.A (A1), R61.1
unnamed: CN7.4, D6.C (K1)
unnamed: CN8.2, CN8.4, CN14.P$1
unnamed: CN8.6, CN8.8, CN14.P$2
unnamed: CN6.1, CN6.2, CN13.P$1
unnamed: CN6.3, CN6.4, CN13.P$2
unnamed: CN5.3, CN5.4, CN12.P$2
unnamed: CN5.1, CN5.2, CN12.P$1
unnamed: CN9.1, CN9.2, F2.1
unnamed: F2.2, SW1.3 (NC)
unnamed: CN9.3, CN9.4, CN15.3, CN15.4
unnamed: D4.A (A1), R59.1
unnamed: CN15.1, CN15.2, SW1.2 (C)
UI_!TEST!: CN7.9, CN10.2, CN10.3
UI_DDS/!ANALOG!: CN7.13, CN11.2, CN11.3
UI_INT/!EXT!: CN7.12, SW4.2 (C)
UI_SYNC_C: CN7.5, CN8.1
UI_SYNC_E: CN7.6, CN8.5
UI_SYNC_N: CN7.8, CN8.7
UI_SYNC_P: CN7.7, CN8.3
UI_VD+3V3: CN7.1, R59.2, R60.2, R61.2
UI_X1/!X2!: CN7.11, SW3.2 (C)
UI_X1/!X10!: CN7.10, SW2.2 (C)

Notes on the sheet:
UI/OUTPUT
WARNING IND.: LowBattery
INFO IND.: External Input
EXT(up)/INT(down)
x2(up)/x1(down)
x10(up)/x1(down)
NORMAL
TEST
DDS
ANALOG
SYNC OUT
ISOLATED
DIRECT
CURRENT MON OUT
EXT SIG IN
Battery Side
Supply Side
UI Part
